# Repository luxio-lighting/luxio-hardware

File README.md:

<div align="center">
  
  <h1>Luxio Hardware</h1>
</div>

| Model ID | DC Input | USB-C Input | Button | Chip | PSRAM | Flash Size |
| --- | --- | --- | --- | --- | --- | --- |
| [LX0001](LX0001/) | 5V — 24V | ✅ 5V | ✅ | ESP32-S3 | None | 4MB |
| [LX0002](LX0002/) | — | ✅ 5V | ✅ | ESP32-S3FH4R2 | 2MB | 4MB |

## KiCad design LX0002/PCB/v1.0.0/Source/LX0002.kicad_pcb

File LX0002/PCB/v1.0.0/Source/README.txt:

LX0002 v1.0.0 source

Open LX0002.kicad_pro using KiCad 10. The native schematic, routed board,
project settings, rules, custom libraries and supplier models are authoritative.
The design is two-layer with all 55 fitted components on top. It is not yet
qualified by assembled-board testing; see first-article-validation.md.

Data files
  parts.json / connections.csv: component and electrical connection inventory.
  core_parts.json, io_parts.json, power_parts.json: schematic-generator inputs.
  placement.json / mechanical.json: frozen placements and mechanical datums.
  *_layout.json: captured routing, reference areas and silkscreen.

Tools
  generate.py: regenerate schematic sheets and component inventory.
  build_board.py: rebuilds an UNROUTED board; use a scratch copy when rebuilding.
  author_routes.py: restores captured routing and ground/reference regions.
  sync_board_metadata.py: synchronizes fields and named no-connect nets.
  apply_silkscreen.py: applies the saved label positions.
  board_appearance.py: applies the intended stackup and black-mask appearance.
  verify_circuit.py / verify_design.py: independent topology and geometry checks.
  export_manufacturing.py: read-only source validation and staged manufacturing
    export; requires no ERC, DRC, schematic parity or unconnected findings.
  create_preview_step_models.py: converts the existing approximate antenna and
    switch VRML geometry into matching STEP solids.
  export_mechanical.py: native populated STEP/GLB and millimeter STL reference;
    verifies every fitted reference and preserves coordinate handedness.
  render_board.py: orthographic renders of the actual exported GLB.
  current_path_mesh.py / current_path_solve_sparse.py: two-layer copper model.
  review_current_paths_adaptive.py / review_3v3_paths.py: resistance reviews.

Use the KiCad bundled Python for tools importing pcbnew and the CadQuery
environment for mechanical export/render tools. The manufacturing exporter
uses the installed KiCad CLI and rsvg-convert. On this Mac:
  KiCad CLI: /Applications/KiCad/KiCad.app/Contents/MacOS/kicad-cli
  KiCad Python: /Applications/KiCad/KiCad.app/Contents/Frameworks/Python.framework/Versions/3.9/bin/python3
  CAD Python: /Users/emile/Git/@luxio-lighting/.tools/cadquery-venv/bin/python

Do not run build_board.py on the routed source merely to refresh exports.
Current routing tables were checked by rebuilding and comparing physical
tracks, vias, pads, keepouts and labels in a separate scratch directory.

Source drawings use KiCad X-right/Y-down. Native STEP uses X-right/Y-negative.
No PCB reflection is applied. The enclosure retains this handedness, and its
print orientation uses proper rotations. The native STEP substrate represents
the 1.51mm dielectric core; finished PCB thickness remains nominally 1.60mm.

Commercial price observations are in ../Assets/pricing. They are dated API
snapshots rather than order quotes. The historical comparison includes MINI-1-N8 and
ESP32-S3FN8 alternatives. This source implements ESP32-S3FH4R2 with 4MB in-package flash and 2MB PSRAM;
the MINI module and FN8 remain historical comparisons.

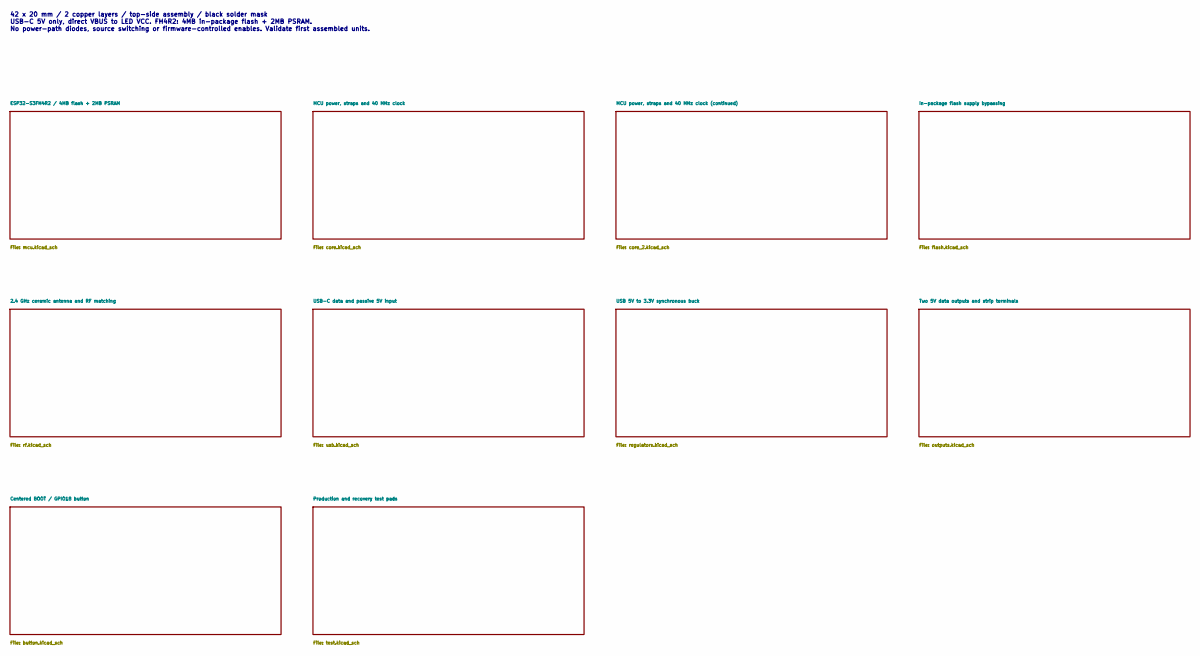
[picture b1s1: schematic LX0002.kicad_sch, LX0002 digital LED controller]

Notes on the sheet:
42 x 20 mm / 2 copper layers / top-side assembly / black solder mask USB-C 5V only, direct VBUS to LED VCC. FH4R2: 4MB in-package flash + 2MB PSRAM. No power-path diodes, source switching or firmware-controlled enables. Validate first assembled units.

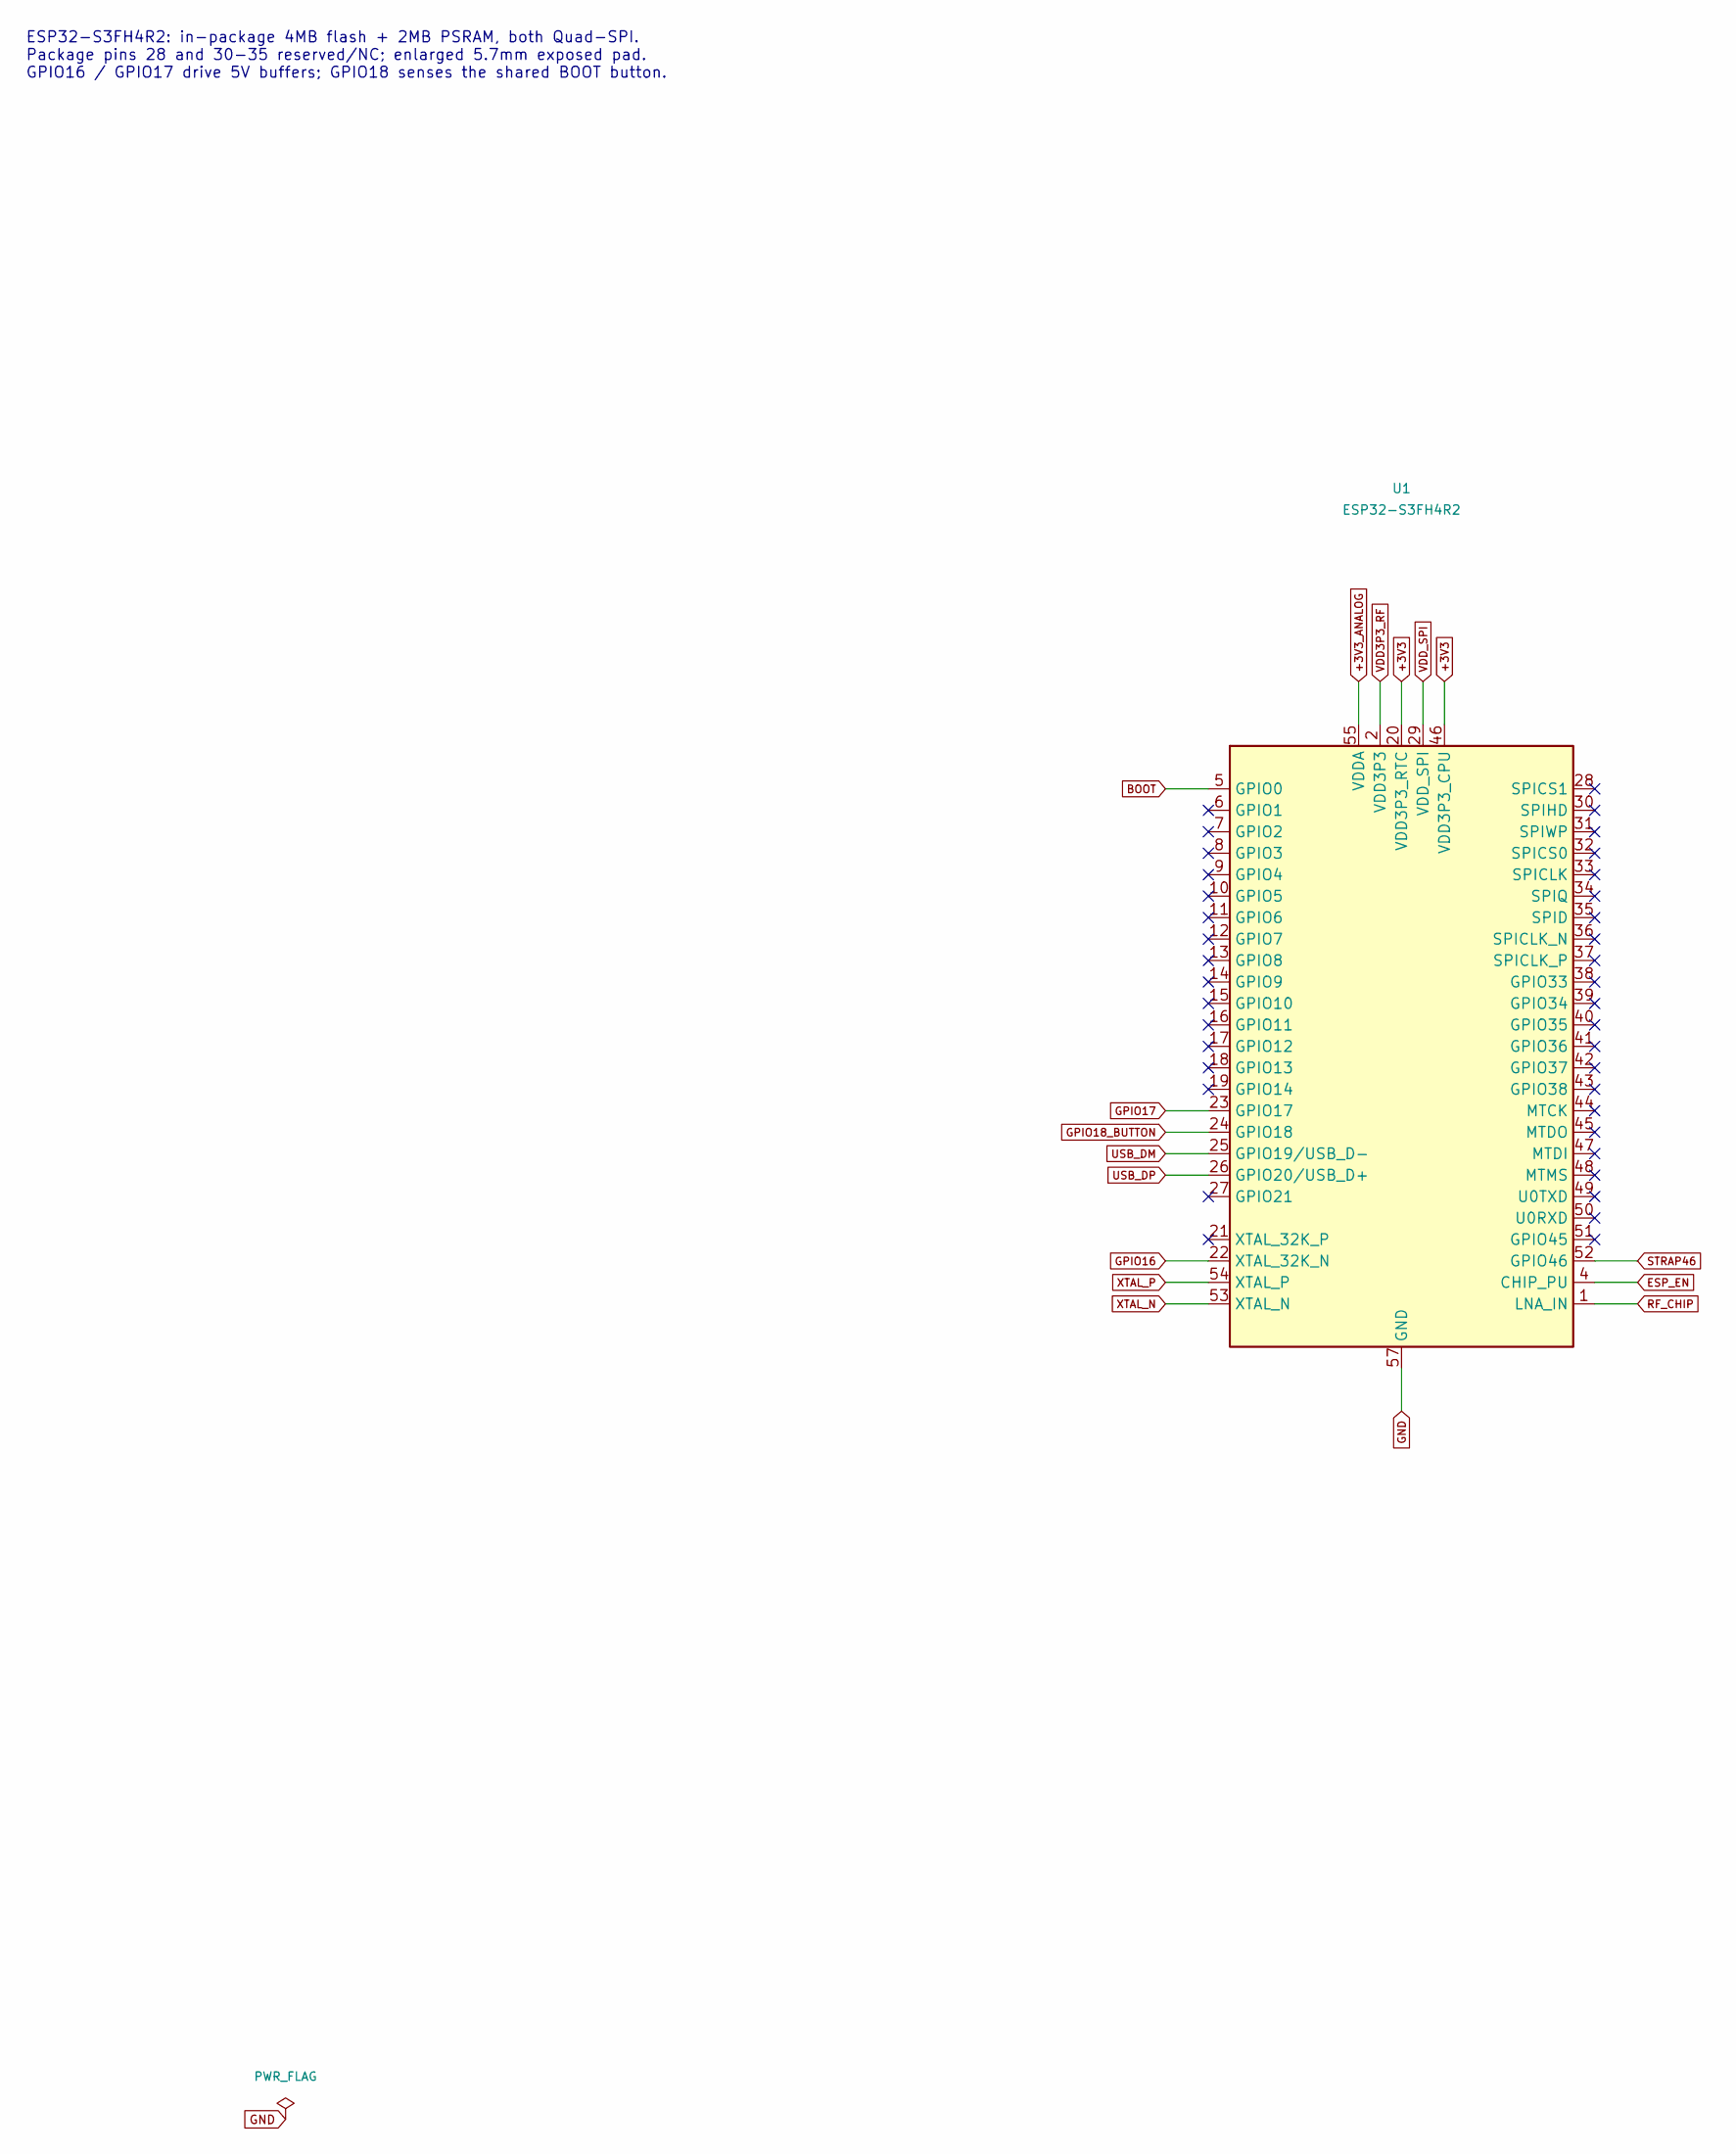
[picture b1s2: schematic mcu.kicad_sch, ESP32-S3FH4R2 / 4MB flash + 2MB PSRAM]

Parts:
U1: ESP32-S3FH4R2; ESP32_S3FH4R2_QFN56_7x7_EP5p7; LCSC C3013940

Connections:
+3V3: U1.20 (VDD3P3_RTC), U1.46 (VDD3P3_CPU); also elsewhere on the board
+3V3_ANALOG: U1.55 (VDDA), U1.56 (VDDA); also elsewhere on the board
BOOT: U1.5 (GPIO0); also elsewhere on the board
ESP_EN: U1.4 (CHIP_PU); also elsewhere on the board
GND: U1.57 (GND); also elsewhere on the board
GPIO16: U1.22 (XTAL_32K_N); also elsewhere on the board
GPIO17: U1.23 (GPIO17); also elsewhere on the board
GPIO18_BUTTON: U1.24 (GPIO18); also elsewhere on the board
RF_CHIP: U1.1 (LNA_IN); also elsewhere on the board
STRAP46: U1.52 (GPIO46); also elsewhere on the board
USB_DM: U1.25 (GPIO19/USB_D-); also elsewhere on the board
USB_DP: U1.26 (GPIO20/USB_D+); also elsewhere on the board
VDD3P3_RF: U1.2 (VDD3P3), U1.3 (VDD3P3); also elsewhere on the board
VDD_SPI: U1.29 (VDD_SPI); also elsewhere on the board
XTAL_N: U1.53 (XTAL_N); also elsewhere on the board
XTAL_P: U1.54 (XTAL_P); also elsewhere on the board

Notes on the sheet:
ESP32-S3FH4R2: in-package 4MB flash + 2MB PSRAM, both Quad-SPI. Package pins 28 and 30-35 reserved/NC; enlarged 5.7mm exposed pad. GPIO16 / GPIO17 drive 5V buffers; GPIO18 senses the shared BOOT button.

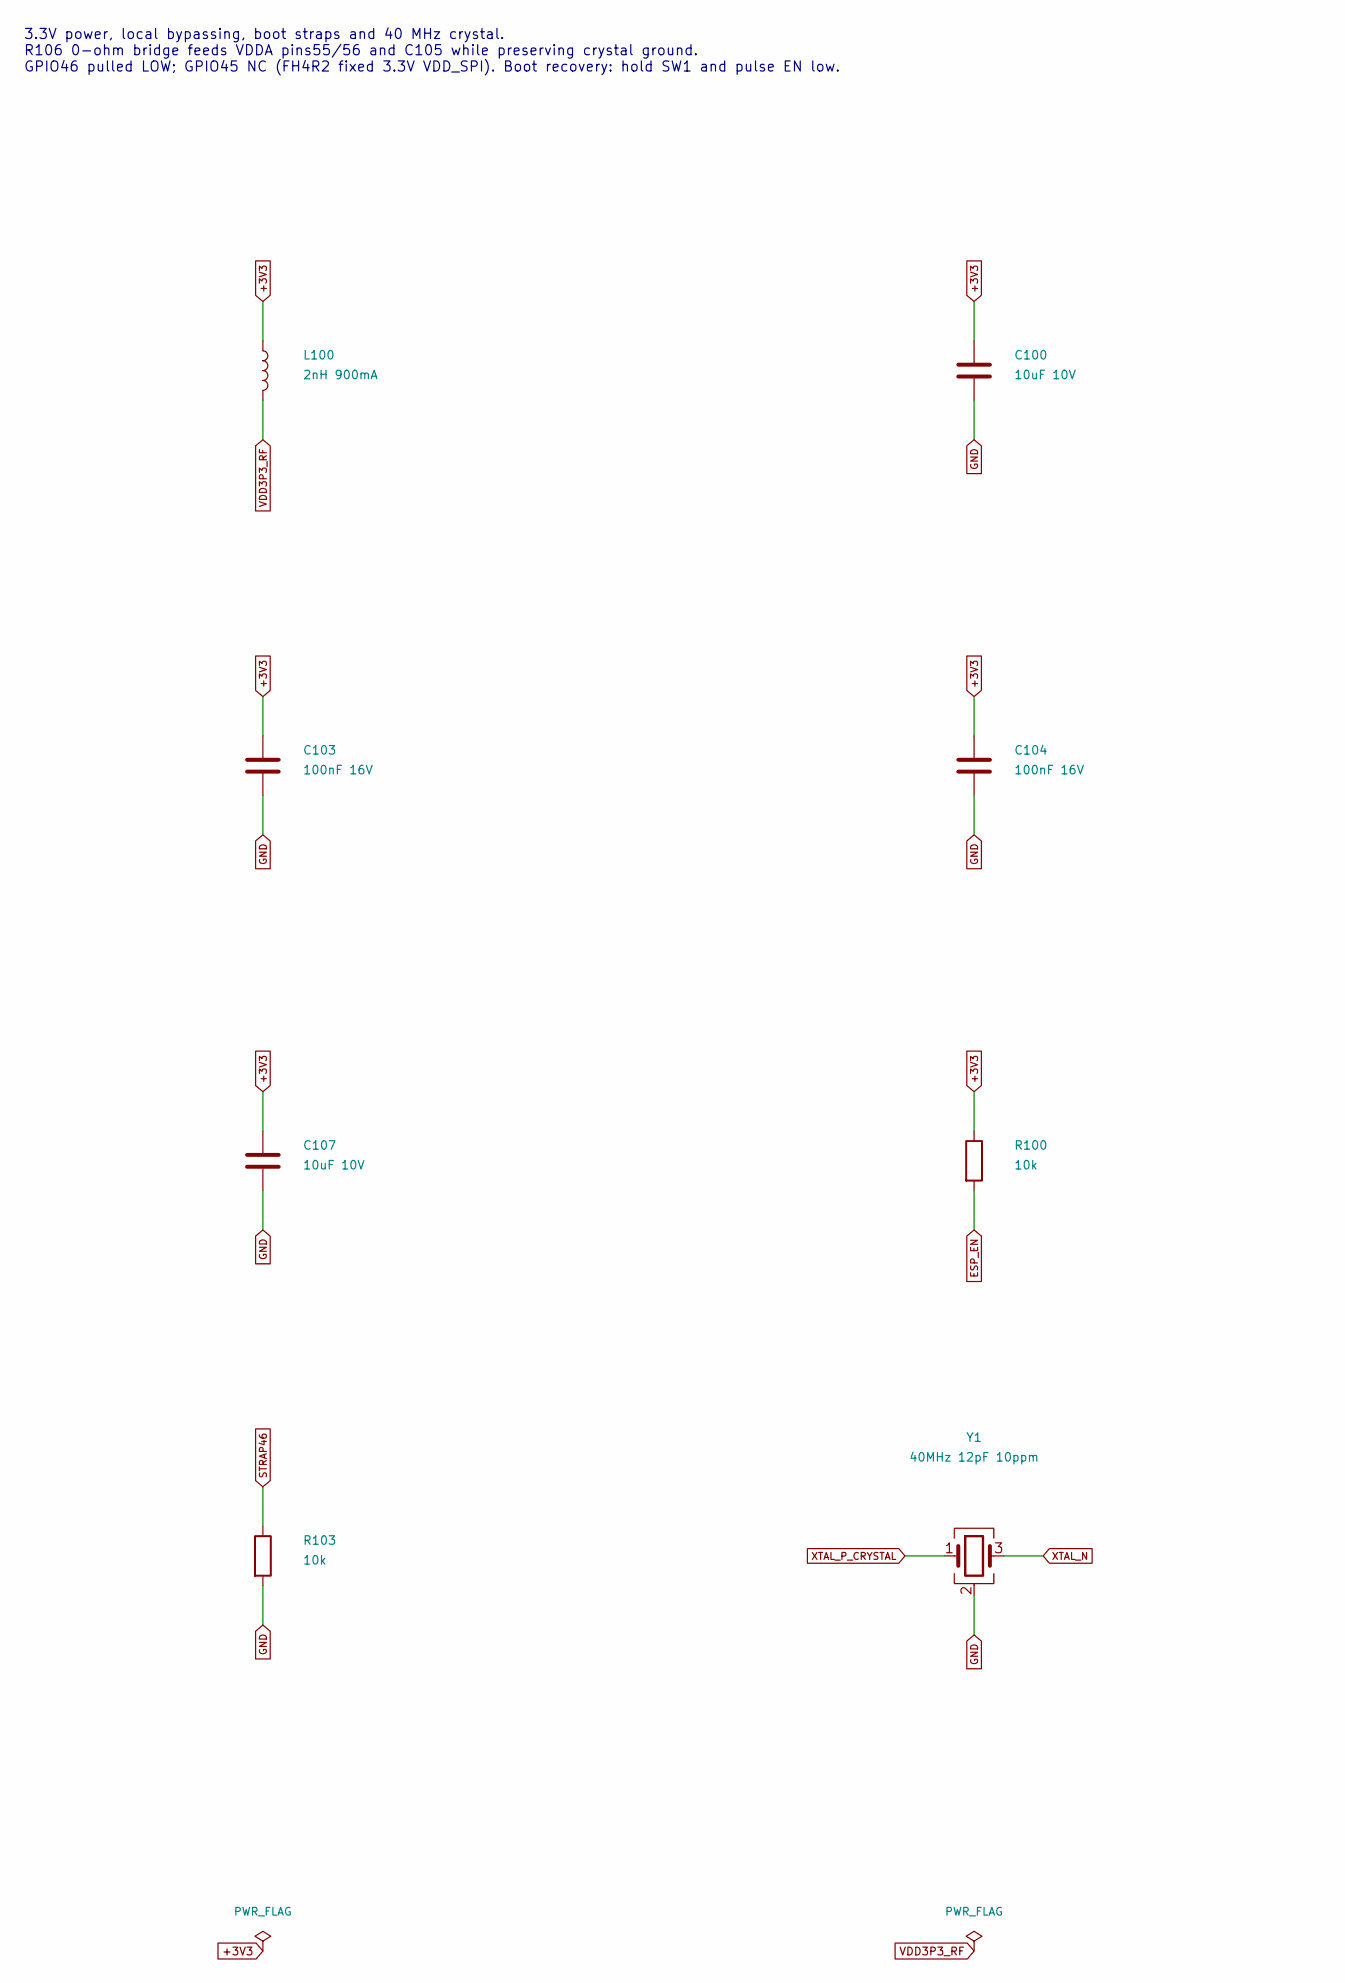
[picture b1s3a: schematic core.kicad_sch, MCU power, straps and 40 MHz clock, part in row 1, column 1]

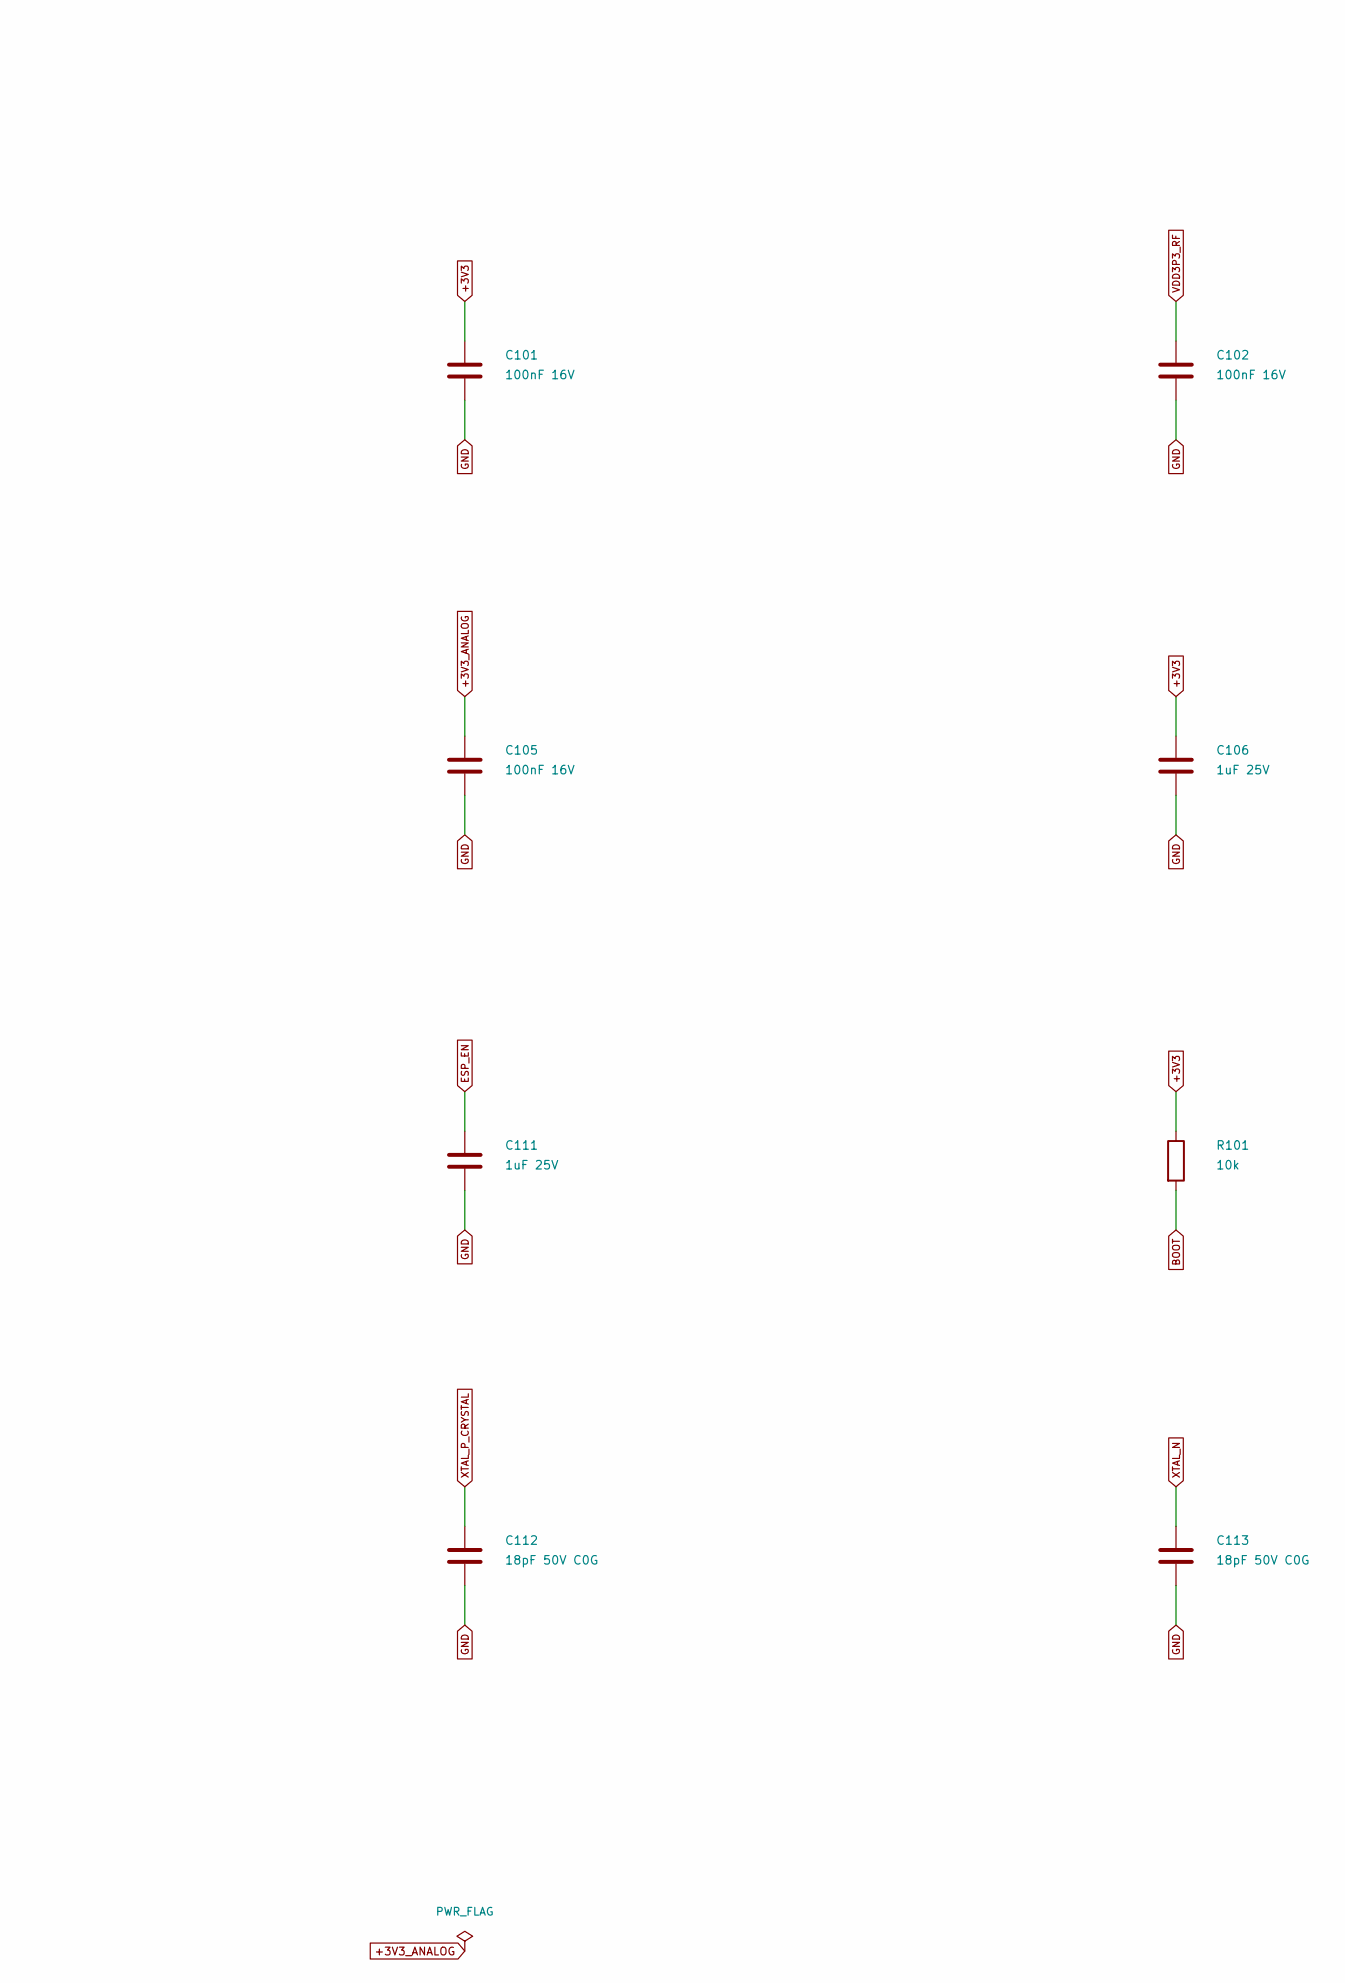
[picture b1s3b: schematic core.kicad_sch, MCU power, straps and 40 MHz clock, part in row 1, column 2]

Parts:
C100, C107: 10uF 10V; C_0603_1608Metric; LCSC C19702
C101, C102, C103, C104, C105: 100nF 16V; C_0402_1005Metric; LCSC C1525
C106, C111: 1uF 25V; C_0402_1005Metric; LCSC C52923
C112, C113: 18pF 50V C0G; C_0402_1005Metric; LCSC C1549
L100: 2nH 900mA; L_0402_1005Metric; LCSC C18216
R100, R101, R103: 10k; R_0402_1005Metric; LCSC C25744
Y1: 40MHz 12pF 10ppm; Crystal_SMD_3225-4Pin_3.2x2.5mm; LCSC C655034

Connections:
+3V3: C100.1, C101.1, C103.1, C104.1, C106.1, C107.1, L100.1, R100.1, R101.1; also elsewhere on the board
+3V3_ANALOG: C105.1; also elsewhere on the board
BOOT: R101.2; also elsewhere on the board
ESP_EN: C111.1, R100.2; also elsewhere on the board
GND: C100.2, C101.2, C102.2, C103.2, C104.2, C105.2, C106.2, C107.2, C111.2, C112.2, C113.2, R103.2, Y1.2 (G), Y1.4 (G); also elsewhere on the board
STRAP46: R103.1; also elsewhere on the board
VDD3P3_RF: C102.1, L100.2; also elsewhere on the board
XTAL_N: C113.1, Y1.3; also elsewhere on the board
XTAL_P_CRYSTAL: C112.1, Y1.1; also elsewhere on the board

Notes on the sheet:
3.3V power, local bypassing, boot straps and 40 MHz crystal. R106 0-ohm bridge feeds VDDA pins55/56 and C105 while preserving crystal ground. GPIO46 pulled LOW; GPIO45 NC (FH4R2 fixed 3.3V VDD_SPI). Boot recovery: hold SW1 and pulse EN low.

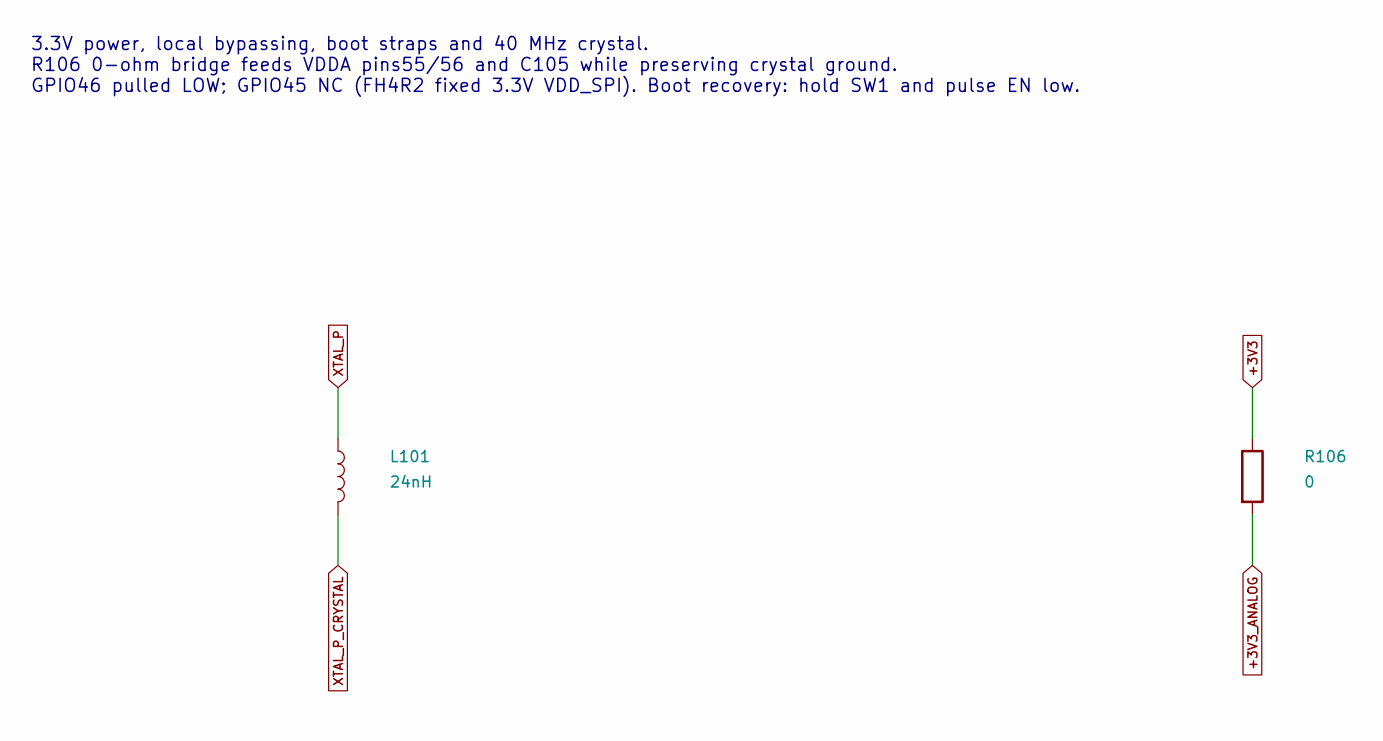
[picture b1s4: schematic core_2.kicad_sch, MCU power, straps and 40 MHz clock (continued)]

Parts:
L101: 24nH; L_0402_1005Metric; LCSC C913699
R106: 0; R_0805_2012Metric; LCSC C17477

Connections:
+3V3: R106.1; also elsewhere on the board
+3V3_ANALOG: R106.2; also elsewhere on the board
XTAL_P: L101.1; also elsewhere on the board
XTAL_P_CRYSTAL: L101.2; also elsewhere on the board

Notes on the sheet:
3.3V power, local bypassing, boot straps and 40 MHz crystal. R106 0-ohm bridge feeds VDDA pins55/56 and C105 while preserving crystal ground. GPIO46 pulled LOW; GPIO45 NC (FH4R2 fixed 3.3V VDD_SPI). Boot recovery: hold SW1 and pulse EN low.

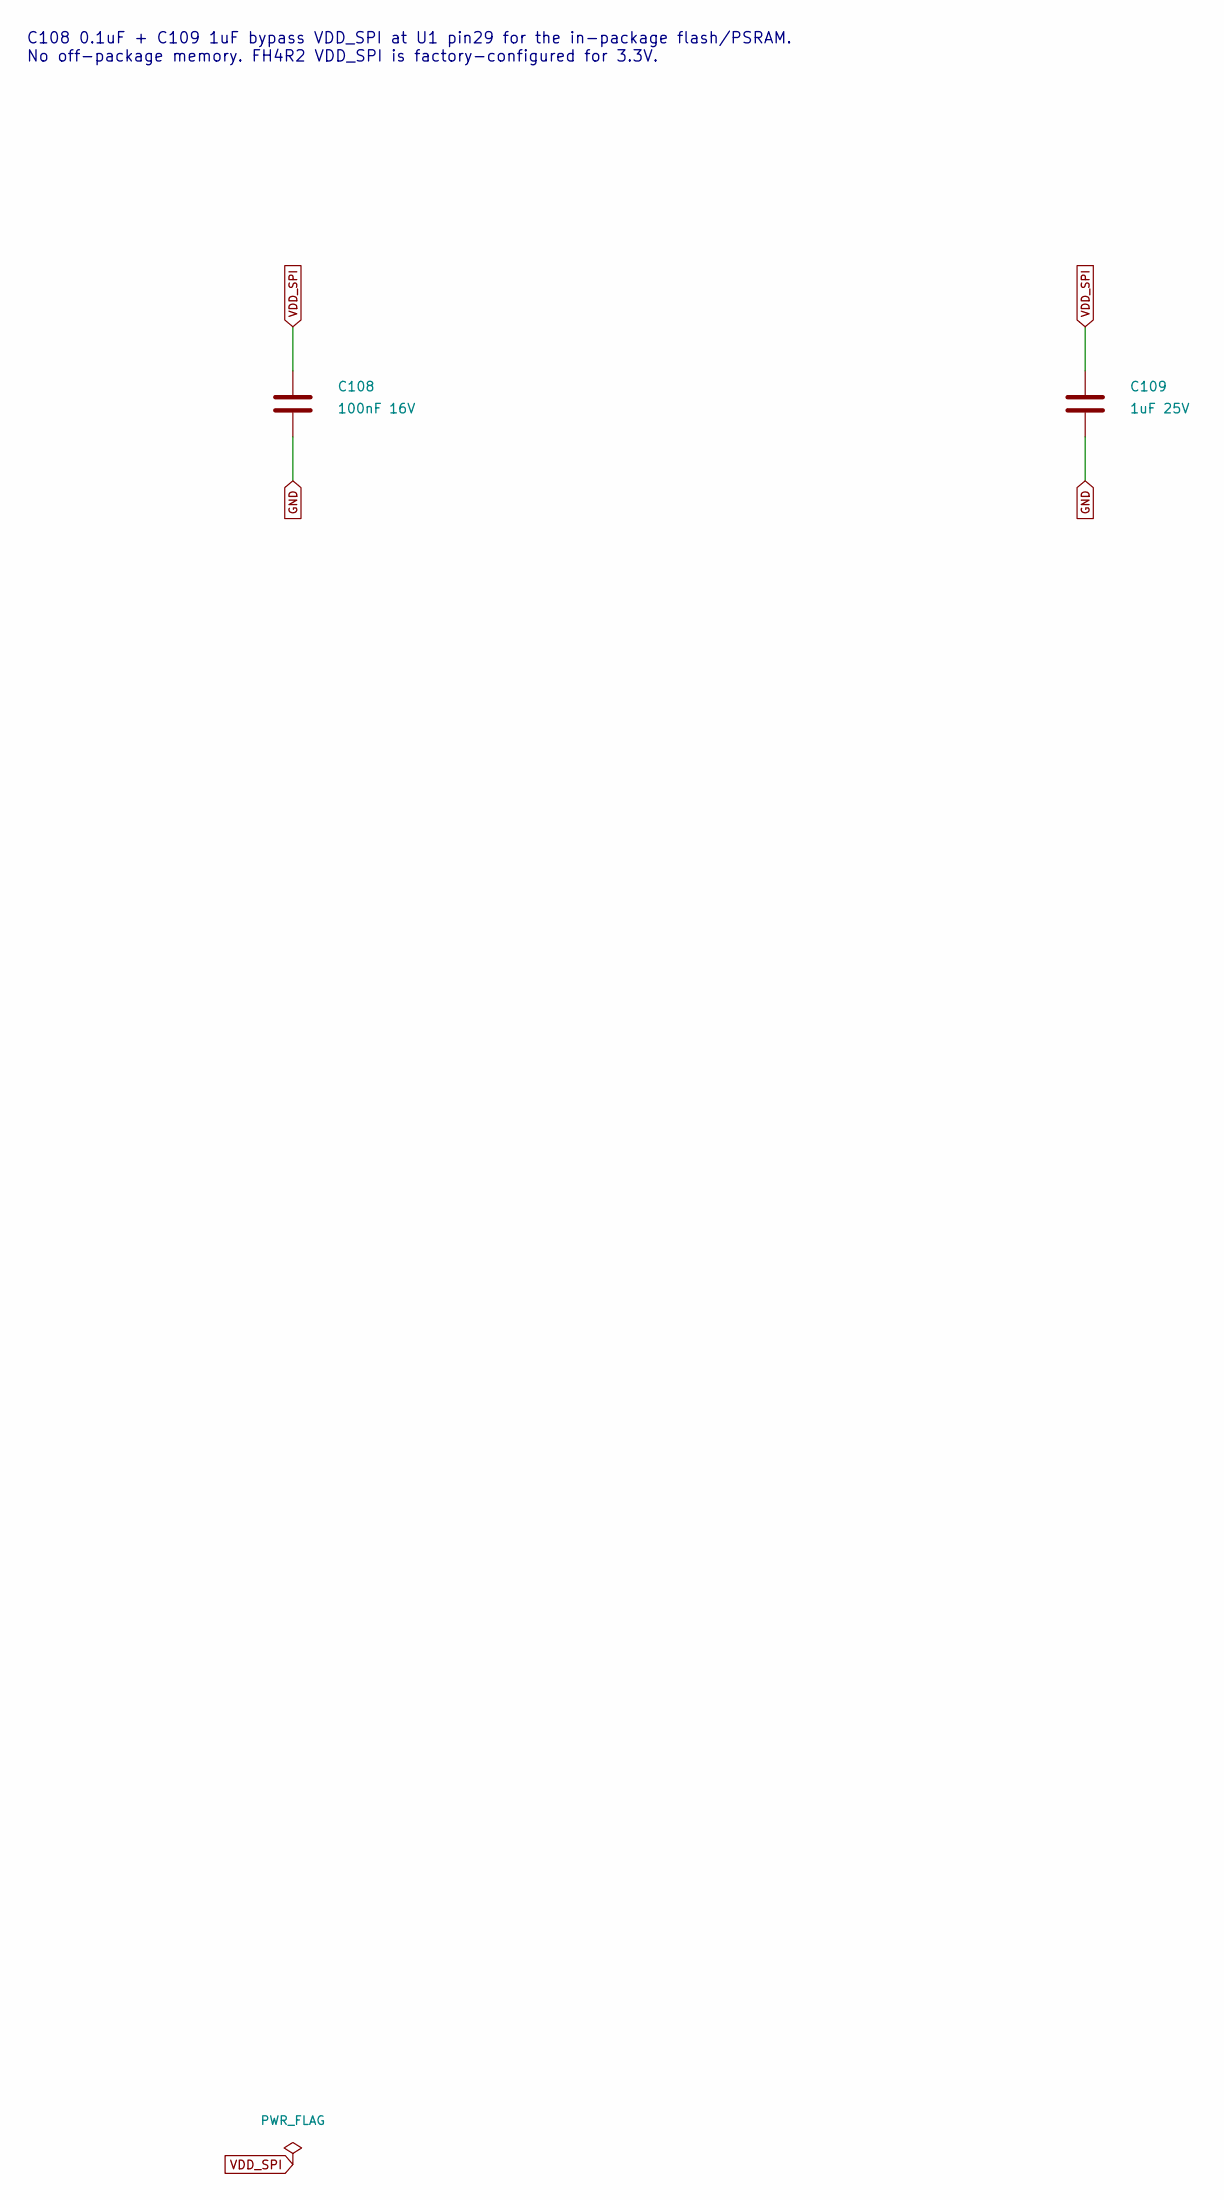
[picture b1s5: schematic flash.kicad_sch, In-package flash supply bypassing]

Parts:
C108: 100nF 16V; C_0402_1005Metric; LCSC C1525
C109: 1uF 25V; C_0402_1005Metric; LCSC C52923

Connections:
GND: C108.2, C109.2; also elsewhere on the board
VDD_SPI: C108.1, C109.1; also elsewhere on the board

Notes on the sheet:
C108 0.1uF + C109 1uF bypass VDD_SPI at U1 pin29 for the in-package flash/PSRAM. No off-package memory. FH4R2 VDD_SPI is factory-configured for 3.3V.

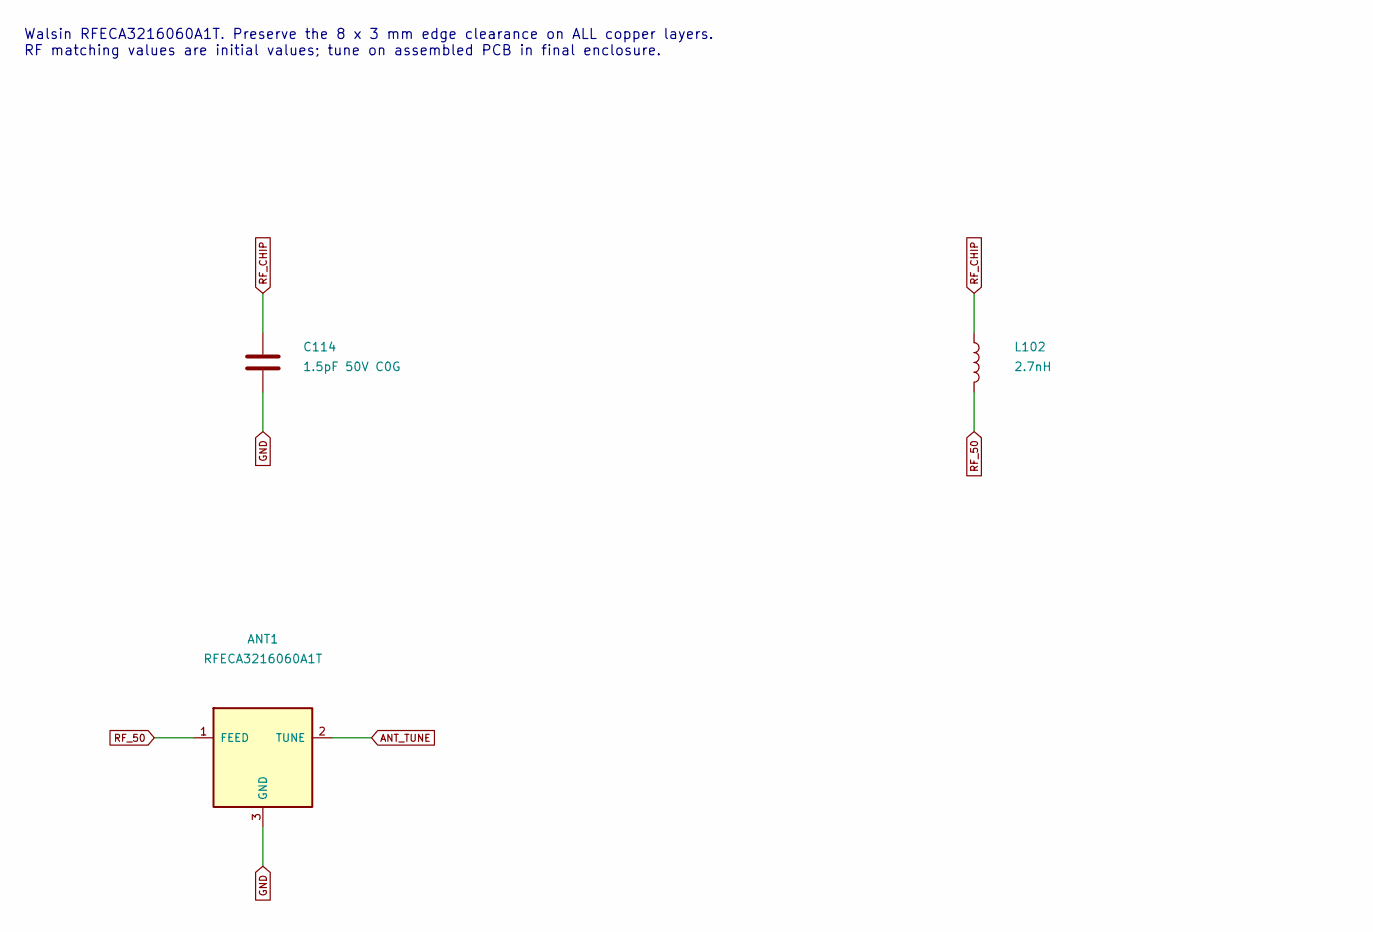
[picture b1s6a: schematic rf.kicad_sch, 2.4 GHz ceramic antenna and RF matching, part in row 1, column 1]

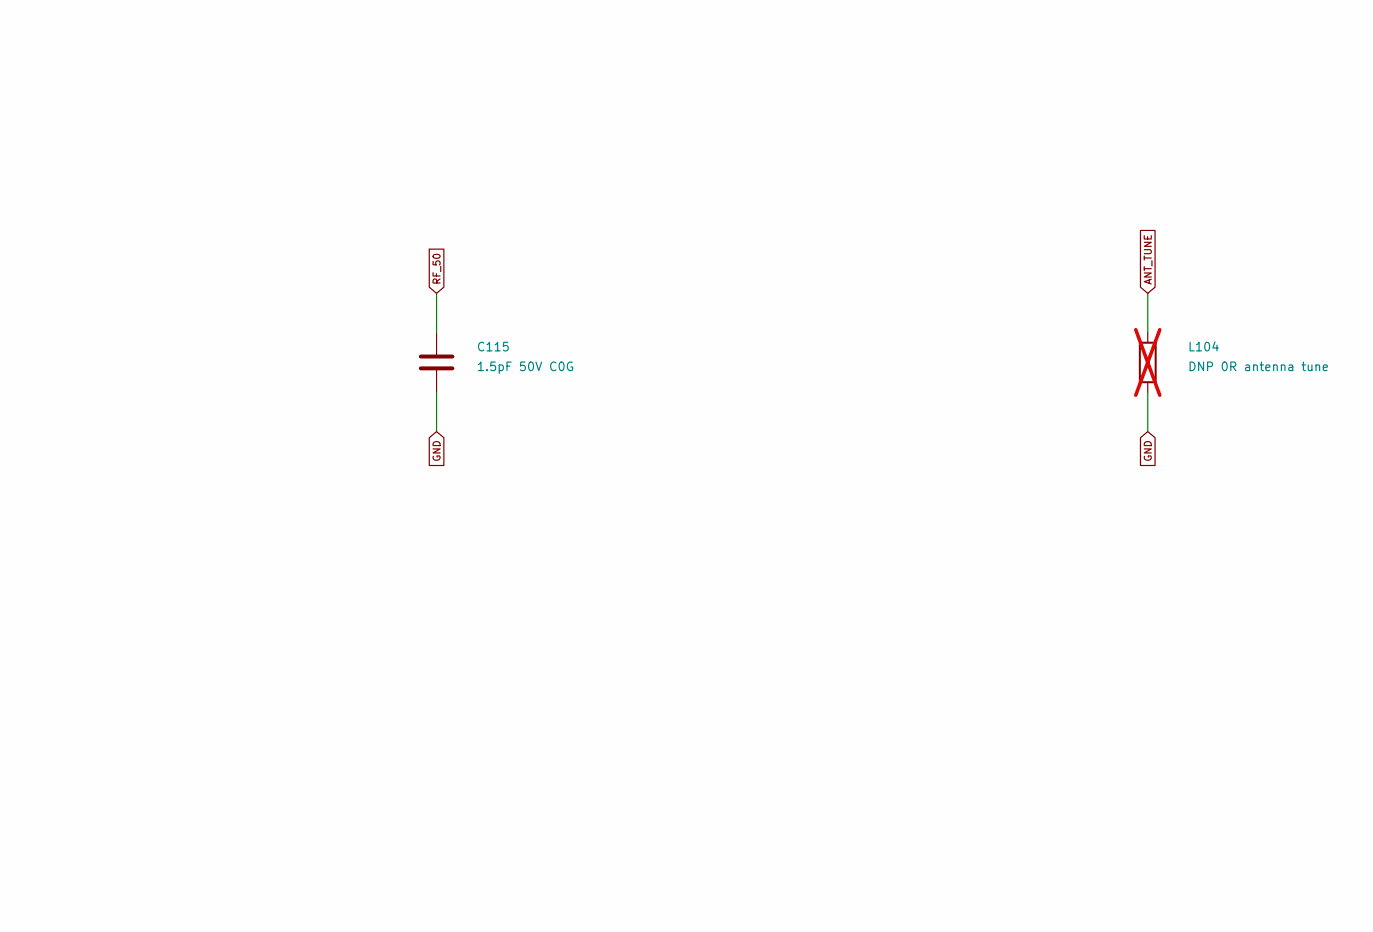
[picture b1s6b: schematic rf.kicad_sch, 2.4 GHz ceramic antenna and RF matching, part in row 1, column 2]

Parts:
ANT1: RFECA3216060A1T; Walsin_RFECA3216060A1T_Type1; LCSC C127620
C114, C115: 1.5pF 50V C0G; C_0201_0603Metric; LCSC C161414
L102: 2.7nH; L_0201_0603Metric; LCSC C7216765
L104: DNP 0R antenna tune; Walsin_RFECA_Tuner_0402; LCSC C17168; not fitted

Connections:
ANT_TUNE: ANT1.2 (TUNE), L104.1
GND: ANT1.3 (GND), C114.2, C115.2, L104.2; also elsewhere on the board
RF_50: ANT1.1 (FEED), C115.1, L102.2
RF_CHIP: C114.1, L102.1; also elsewhere on the board

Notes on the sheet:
Walsin RFECA3216060A1T. Preserve the 8 x 3 mm edge clearance on ALL copper layers. RF matching values are initial values; tune on assembled PCB in final enclosure.
